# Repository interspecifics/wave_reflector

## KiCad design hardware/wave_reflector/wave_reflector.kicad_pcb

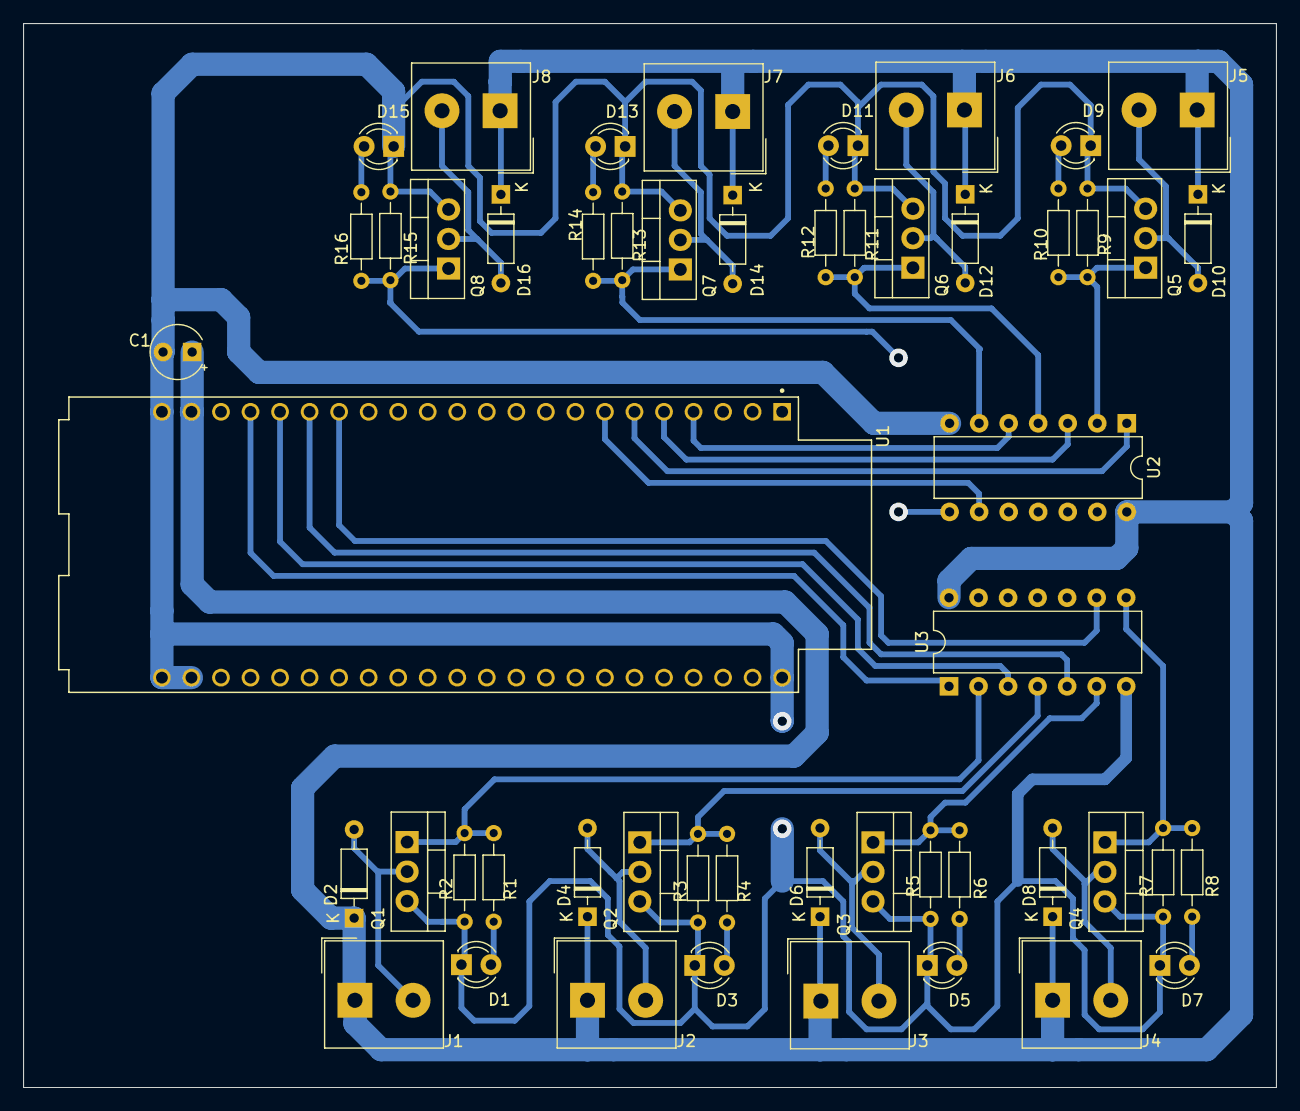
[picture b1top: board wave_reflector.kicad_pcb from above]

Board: 2 copper layers, 107.8 x 91.5 mm, 52 parts (0 on the bottom side), 34 nets.

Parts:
C1: 10uF TANT; CP_Radial_Tantal_D4.5mm_P2.50mm
D1, D3, D5, D7, D9, D11, D13, D15: LED; LED_D3.0mm
D2, D4, D6, D8, D10, D12, D14, D16: 1N4004; D_DO-35_SOD27_P7.62mm_Horizontal
J1: M1_connector; Altech_AK100_1x02_P5.00mm
J2: M2_connector; Altech_AK100_1x02_P5.00mm
J3: M3_connector; Altech_AK100_1x02_P5.00mm
J4: M4_connector; Altech_AK100_1x02_P5.00mm
J5: M5_connector; Altech_AK100_1x02_P5.00mm
J6: M6_connector; Altech_AK100_1x02_P5.00mm
J7: M7_connector; Altech_AK100_1x02_P5.00mm
J8: M8_connector; Altech_AK100_1x02_P5.00mm
Q1, Q2, Q3, Q4, Q5, Q6, Q7, Q8: IRF540N; TO-220-3_Vertical
R1, R2, R3, R4, R5, R6, R7, R8, R9, R10, R11, R12, R13, R14, R15, R16: 1k; R_Axial_DIN0204_L3.6mm_D1.6mm_P7.62mm_Horizontal
U1: ESP32-S2-DEVKITC-1; MODULE_ESP32-S2-DEVKITC-1
U2, U3: 74HC14; DIP-14_W7.62mm

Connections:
GND: C1.2, D1.1 (K), D3.1 (K), D5.1 (K), D7.1 (K), D9.1 (K), D11.1 (K), D13.1 (K), D15.1 (K), Q1.3 (S), Q2.3 (S), Q3.3 (S), Q4.3 (S), Q5.3 (S), Q6.3 (S), Q7.3 (S), Q8.3 (S), R2.2, R3.2, R5.2, R7.2, R9.2, R11.2, R13.2, R15.2, U1.J1_22 (GND_J1_22), U1.J3_1 (GND_J3_1), U1.J3_21 (GND_J3_21), U1.J3_22 (GND_J3_22), U2.7 (GND), U3.7 (GND)
unnamed: D1.2 (A), R1.2
unnamed: D2.2 (A), J1.2, Q1.2 (D)
unnamed: D3.2 (A), R4.2
unnamed: D4.2 (A), J2.2, Q2.2 (D)
unnamed: D5.2 (A), R6.2
unnamed: D6.2 (A), J3.2, Q3.2 (D)
unnamed: D7.2 (A), R8.2
unnamed: D8.2 (A), J4.2, Q4.2 (D)
unnamed: D9.2 (A), R10.2
unnamed: D10.2 (A), J5.2, Q5.2 (D)
unnamed: D11.2 (A), R12.2
unnamed: D12.2 (A), J6.2, Q6.2 (D)
unnamed: D13.2 (A), R14.2
unnamed: D14.2 (A), J7.2, Q7.2 (D)
unnamed: D15.2 (A), R16.2
unnamed: D16.2 (A), J8.2, Q8.2 (D)
unnamed: U1.J1_4 (GPIO4), U2.5
unnamed: U1.J1_5 (GPIO5), U2.3
unnamed: U1.J1_6 (GPIO6), U2.1
unnamed: U1.J1_7 (GPIO7), U2.9
unnamed: U1.J1_16 (GPIO10), U3.9
unnamed: U1.J1_17 (GPIO11), U3.5
unnamed: U1.J1_18 (GPIO12), U3.3
unnamed: U1.J1_19 (GPIO13), U3.1
SGN_A1: Q1.1 (G), R1.1, R2.1, U3.2
SGN_A2: Q2.1 (G), R3.1, R4.1, U3.4
SGN_A3: Q3.1 (G), R5.1, R6.1, U3.6
SGN_A4: Q4.1 (G), R7.1, R8.1, U3.8
SGN_A5: Q5.1 (G), R9.1, R10.1, U2.2
SGN_A6: Q6.1 (G), R11.1, R12.1, U2.4
SGN_A7: Q7.1 (G), R13.1, R14.1, U2.6
SGN_A8: Q8.1 (G), R15.1, R16.1, U2.8
VCC: C1.1, D2.1 (K), D4.1 (K), D6.1 (K), D8.1 (K), D10.1 (K), D12.1 (K), D14.1 (K), D16.1 (K), J1.1, J2.1, J3.1, J4.1, J5.1, J6.1, J7.1, J8.1, U1.J1_21 (VCC_5V), U2.14 (VCC), U3.14 (VCC)

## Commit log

2024-06-20 primer comentario
2024-06-26 modelos de comportamiento de pulsar y granuladores en stream
2024-06-27 firmware receivers
    <>
2024-06-27 updated PCB
    now with PCB
2024-07-04 send receive
    UDP
2024-07-08 commit python scripts
2024-07-15 update to include reverse engineering and latest changes
2024-08-13 august udp version wip
2024-08-16 updates para estabilizar el comportamiento del análisis de ICA y PSD multiple
2024-08-16 w/home
2024-08-27 installation working version update
2024-08-28 sound multichannel dac
2024-08-29 working version
2024-09-21 added gitignore
2024-09-21 gitignore dep
2024-09-21 fixed ICA_gradient osc connection to max-msp
